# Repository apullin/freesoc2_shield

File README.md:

# freesoc2_shield
A generic shield template for the FreeSoC 2 board.

Work in progress!

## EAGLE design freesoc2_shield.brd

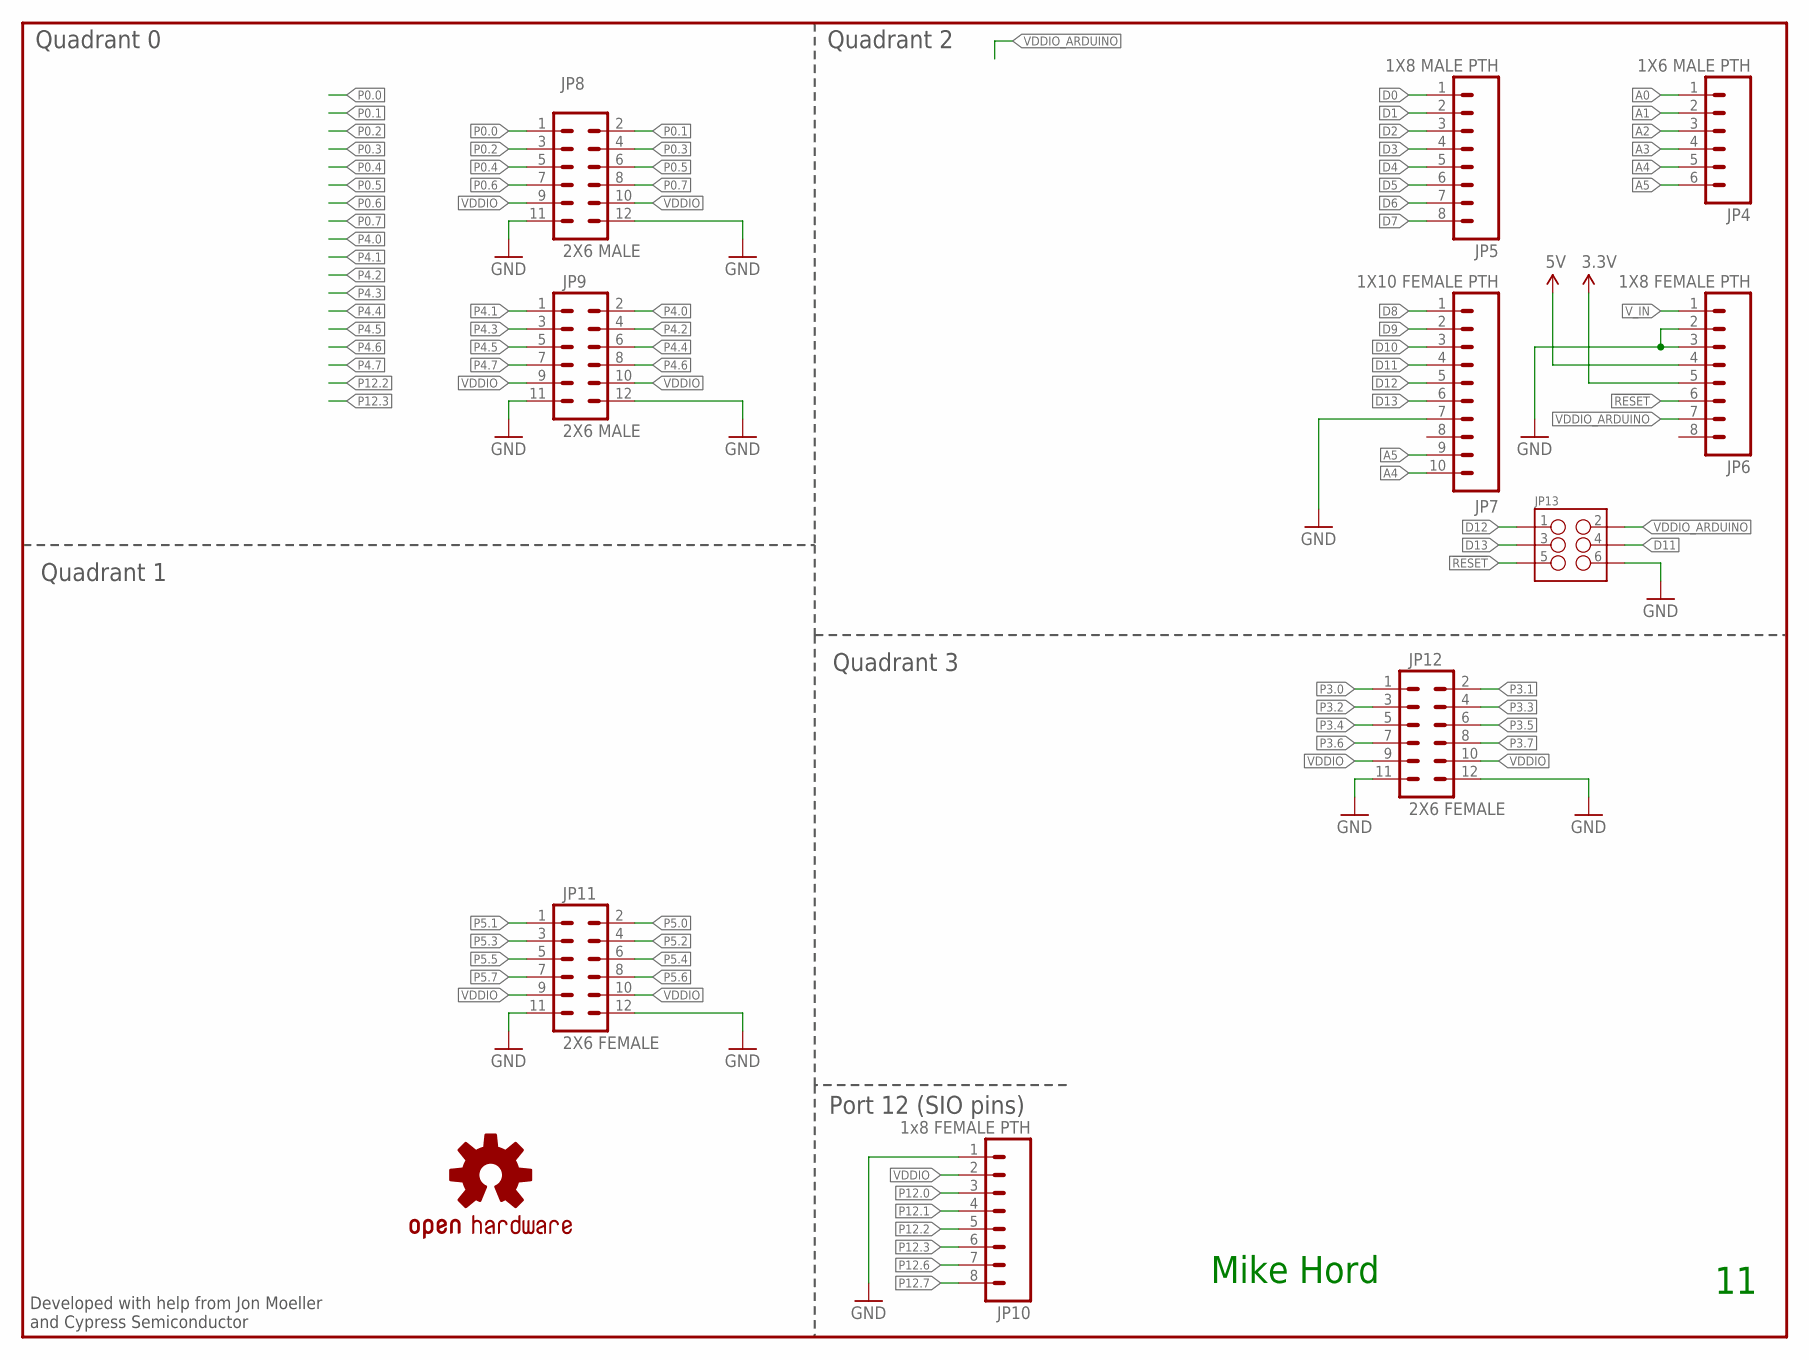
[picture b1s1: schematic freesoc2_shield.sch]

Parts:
FRAME1: FRAME-LETTERNO_PACKAGE; DUMMY
JP4: 1X6 MALE PTH; 1X06-SIP_LOCK
JP5: 1X8 MALE PTH; 1X08_LOCK
JP6: 1X8 FEMALE PTH; 1X08_LOCK
JP7: 1X10 FEMALE PTH; 1X10_LOCK
JP8, JP9: 2X6 MALE; 2X6
JP10: 1x8 FEMALE PTH; 1X08_LOCK
JP11, JP12: 2X6 FEMALE; 2X6
JP13: M03X22X3_SILK_MALE_PTH; 2X3
LOGO2: OSHW-LOGOS; OSHW-LOGO-S

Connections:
3.3V: JP6.5
5V: JP6.4
!RESET: JP6.6, JP13.5
A0: JP4.1
A1: JP4.2
A2: JP4.3
A3: JP4.4
A4: JP4.5, JP7.10
A5: JP4.6, JP7.9
D0: JP5.1
D1: JP5.2
D2: JP5.3
D3: JP5.4
D4: JP5.5
D5: JP5.6
D6: JP5.7
D7: JP5.8
D8: JP7.1
D9: JP7.2
D10: JP7.3
D11: JP7.4, JP13.4
D12: JP7.5, JP13.1
D13: JP7.6, JP13.3
GND: JP6.2, JP6.3, JP7.7, JP8.11, JP8.12, JP9.11, JP9.12, JP10.1, JP11.11, JP11.12, JP12.11, JP12.12, JP13.6
P0.0: JP8.1
P0.1: JP8.2
P0.2: JP8.3
P0.3: JP8.4
P0.4: JP8.5
P0.5: JP8.6
P0.6: JP8.7
P0.7: JP8.8
P3.0: JP12.1
P3.1: JP12.2
P3.2: JP12.3
P3.3: JP12.4
P3.4: JP12.5
P3.5: JP12.6
P3.6: JP12.7
P3.7: JP12.8
P4.0: JP9.2
P4.1: JP9.1
P4.2: JP9.4
P4.3: JP9.3
P4.4: JP9.6
P4.5: JP9.5
P4.6: JP9.8
P4.7: JP9.7
P5.0: JP11.2
P5.1: JP11.1
P5.2: JP11.4
P5.3: JP11.3
P5.4: JP11.6
P5.5: JP11.5
P5.6: JP11.8
P5.7: JP11.7
P12.0: JP10.3
P12.1: JP10.4
P12.2: JP10.5
P12.3: JP10.6
P12.6: JP10.7
P12.7: JP10.8
VDDIO: JP8.9, JP8.10, JP9.9, JP9.10, JP10.2, JP11.9, JP11.10, JP12.9, JP12.10
VDDIO_ARDUINO: JP6.7, JP13.2
V_IN: JP6.1

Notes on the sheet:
Quadrant 1
Quadrant 2
Quadrant 0
Quadrant 3
Port 12 (SIO pins)
Developed with help from Jon Moeller and Cypress Semiconductor
Mike Hord

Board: 4 copper layers, 12 parts (0 on the bottom side), 9 nets, no tracks yet.

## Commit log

2016-01-19 Initial commit of files.

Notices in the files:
parts and their libraries:
SparkFun-Aesthetics: Licensing: Creative Commons ShareAlike 4.0 International - https://creativecommons.org/licenses/by-sa/4.0
SparkFun-Aesthetics: Released under the Creative Commons Attribution Share-Alike 4.0 License
SparkFun-Aesthetics: https://creativecommons.org/licenses/by-sa/4.0
